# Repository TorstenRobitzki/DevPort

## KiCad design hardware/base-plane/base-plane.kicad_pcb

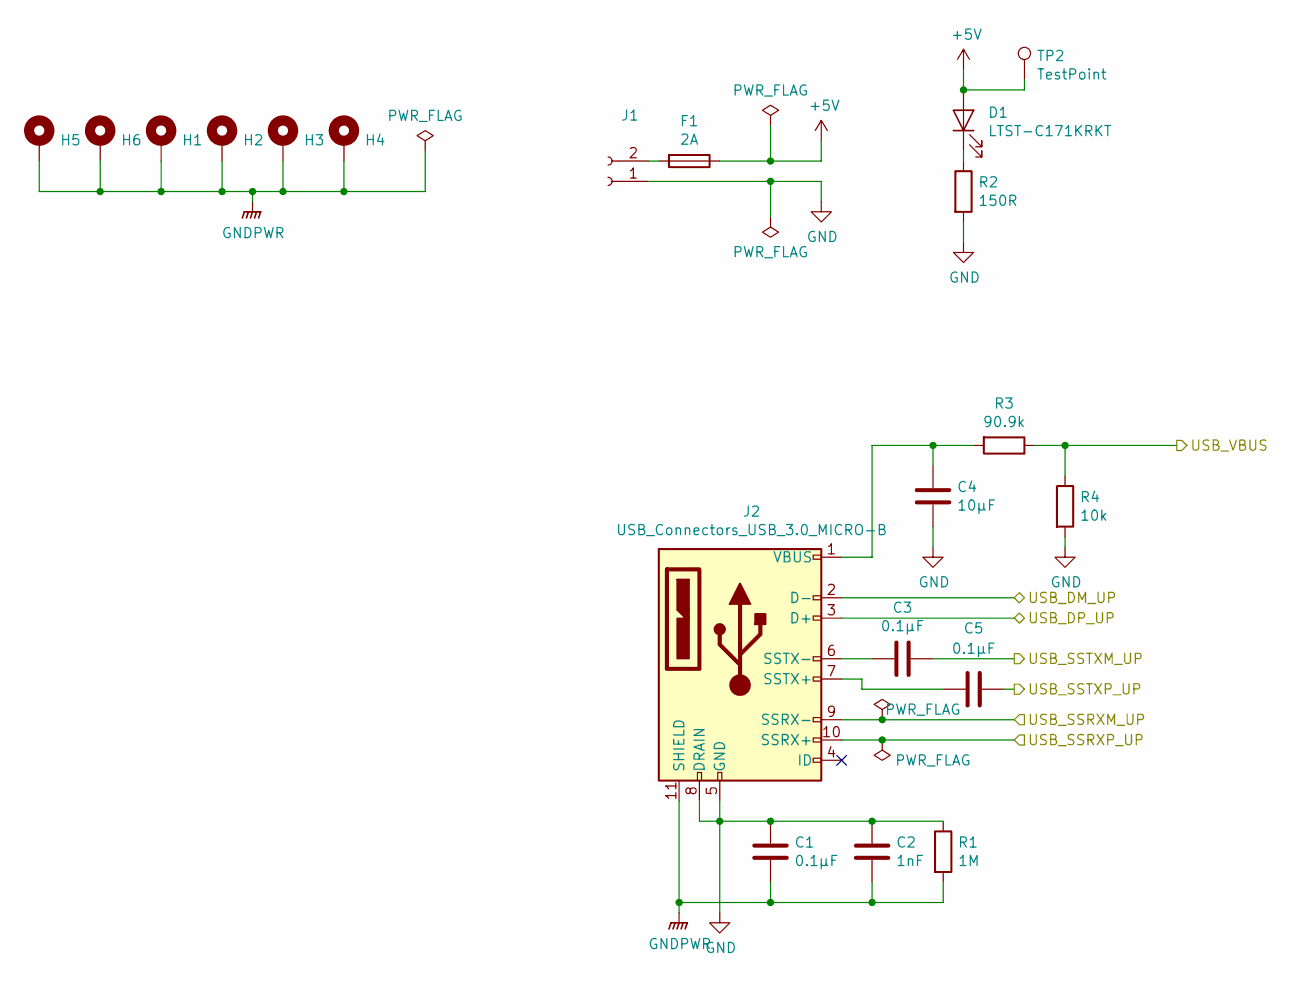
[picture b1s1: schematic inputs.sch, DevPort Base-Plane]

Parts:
C1, C3, C5: 0.1µF; C_0603_1608Metric
C2: 1nF; C_0603_1608Metric
C4: 10µF; C_0603_1608Metric
D1: LTST-C171KRKT; LED_0805_2012Metric
F1: 2A; Fuse_0603_1608Metric
H1, H2, H3, H4, H5, H6: MountingHole_Pad; MountingHole_3.2mm_M3_Pad_Via
J1: Conn_01x02_Female; Molex_Mini-Fit_Jr_5566-02A_2x01_P4.20mm_Vertical
J2: USB_Connectors_USB_3.0_MICRO-B; 692622420101
R1: 1M; R_0603_1608Metric
R2: 150R; R_0603_1608Metric
R3: 90.9k; R_0603_1608Metric
R4: 10k; R_0603_1608Metric
TP2: TestPoint; TestPoint_THTPad_1.0x1.0mm_Drill0.5mm

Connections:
+5V: D1.2 (A), F1.1, TP2.1; also elsewhere on the board
/hub/USB_DM_UP: J2.2 (D-); also elsewhere on the board
/hub/USB_DP_UP: J2.3 (D+); also elsewhere on the board
/hub/USB_SSRXM_UP: J2.9 (SSRX-); also elsewhere on the board
/hub/USB_SSRXP_UP: J2.10 (SSRX+); also elsewhere on the board
/hub/USB_SSTXM_UP: C3.1; also elsewhere on the board
/hub/USB_SSTXP_UP: C5.1; also elsewhere on the board
/hub/USB_VBUS: R3.1, R4.1; also elsewhere on the board
GND: C1.1, C2.1, C4.1, J1.1, J2.5 (GND), J2.8 (DRAIN), R1.1, R2.2, R4.2; also elsewhere on the board
GNDPWR: C1.2, C2.2, H1.1, H2.1, H3.1, H4.1, H5.1, H6.1, J2.11 (SHIELD), R1.2; also elsewhere on the board
unnamed: C3.2, J2.6 (SSTX-)
unnamed: C4.2, J2.1 (VBUS), R3.2
unnamed: C5.2, J2.7 (SSTX+)
unnamed: D1.1 (K), R2.1
unnamed: F1.2, J1.2

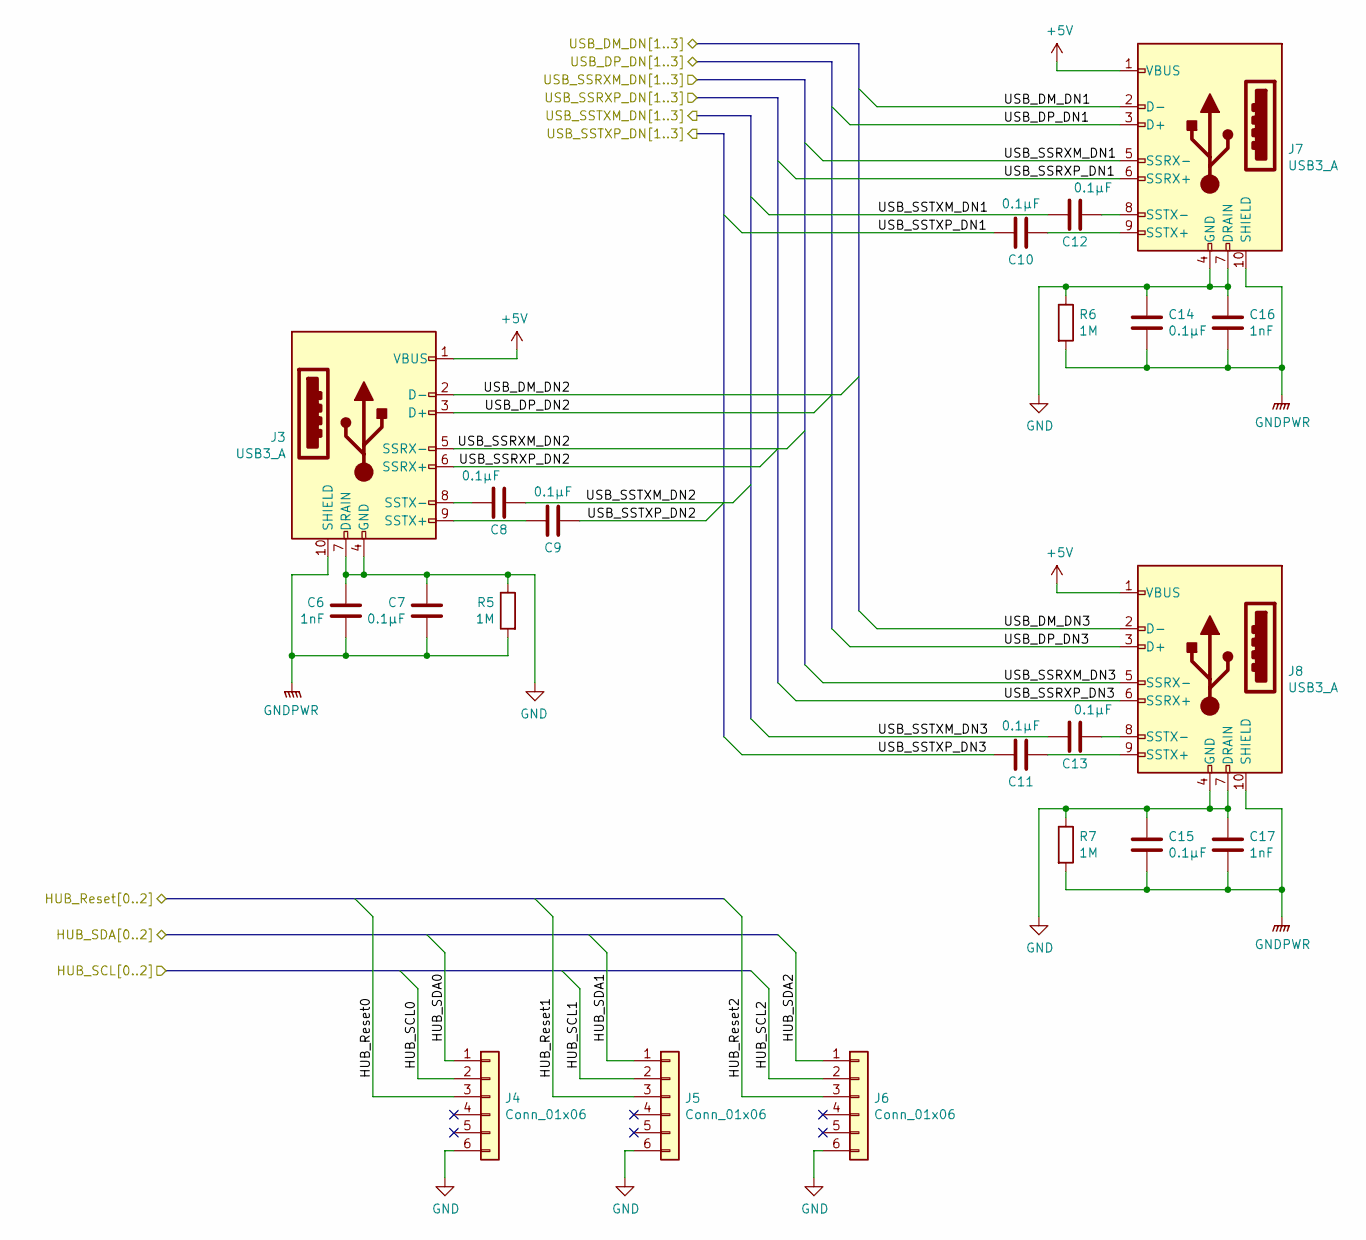
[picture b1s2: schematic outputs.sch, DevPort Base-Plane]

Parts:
C6, C16, C17: 1nF; C_0603_1608Metric
C7, C8, C9, C10, C11, C12, C13, C14, C15: 0.1µF; C_0603_1608Metric
J3, J7, J8: USB3_A; LUSB-3593-00
J4, J5, J6: Conn_01x06; PinHeader_2x03_P1.27mm_Vertical_SMD
R5, R6, R7: 1M; R_0603_1608Metric

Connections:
+5V: J3.1 (VBUS), J7.1 (VBUS), J8.1 (VBUS); also elsewhere on the board
/controller/HUB_Reset0: J4.3; also elsewhere on the board
/controller/HUB_Reset1: J5.3; also elsewhere on the board
/controller/HUB_Reset2: J6.3; also elsewhere on the board
/controller/HUB_SCL0: J4.2; also elsewhere on the board
/controller/HUB_SCL1: J5.2; also elsewhere on the board
/controller/HUB_SCL2: J6.2; also elsewhere on the board
/controller/HUB_SDA0: J4.1; also elsewhere on the board
/controller/HUB_SDA1: J5.1; also elsewhere on the board
/controller/HUB_SDA2: J6.1; also elsewhere on the board
/hub/USB_DM_DN1: J7.2 (D-); also elsewhere on the board
/hub/USB_DM_DN2: J3.2 (D-); also elsewhere on the board
/hub/USB_DM_DN3: J8.2 (D-); also elsewhere on the board
/hub/USB_DP_DN1: J7.3 (D+); also elsewhere on the board
/hub/USB_DP_DN2: J3.3 (D+); also elsewhere on the board
/hub/USB_DP_DN3: J8.3 (D+); also elsewhere on the board
/hub/USB_SSRXM_DN1: J7.5 (SSRX-); also elsewhere on the board
/hub/USB_SSRXM_DN2: J3.5 (SSRX-); also elsewhere on the board
/hub/USB_SSRXM_DN3: J8.5 (SSRX-); also elsewhere on the board
/hub/USB_SSRXP_DN1: J7.6 (SSRX+); also elsewhere on the board
/hub/USB_SSRXP_DN2: J3.6 (SSRX+); also elsewhere on the board
/hub/USB_SSRXP_DN3: J8.6 (SSRX+); also elsewhere on the board
/hub/USB_SSTXM_DN1: C12.2; also elsewhere on the board
/hub/USB_SSTXM_DN2: C8.2; also elsewhere on the board
/hub/USB_SSTXM_DN3: C13.2; also elsewhere on the board
/hub/USB_SSTXP_DN1: C10.2; also elsewhere on the board
/hub/USB_SSTXP_DN2: C9.2; also elsewhere on the board
/hub/USB_SSTXP_DN3: C11.2; also elsewhere on the board
GND: C6.1, C7.1, C14.1, C15.1, C16.1, C17.1, J3.4 (GND), J3.7 (DRAIN), J4.6, J5.6, J6.6, J7.4 (GND), J7.7 (DRAIN), J8.4 (GND), J8.7 (DRAIN), R5.1, R6.1, R7.1; also elsewhere on the board
GNDPWR: C6.2, C7.2, C14.2, C15.2, C16.2, C17.2, J3.10 (SHIELD), J7.10 (SHIELD), J8.10 (SHIELD), R5.2, R6.2, R7.2; also elsewhere on the board
unnamed: C8.1, J3.8 (SSTX-)
unnamed: C9.1, J3.9 (SSTX+)
unnamed: C10.1, J7.9 (SSTX+)
unnamed: C11.1, J8.9 (SSTX+)
unnamed: C12.1, J7.8 (SSTX-)
unnamed: C13.1, J8.8 (SSTX-)

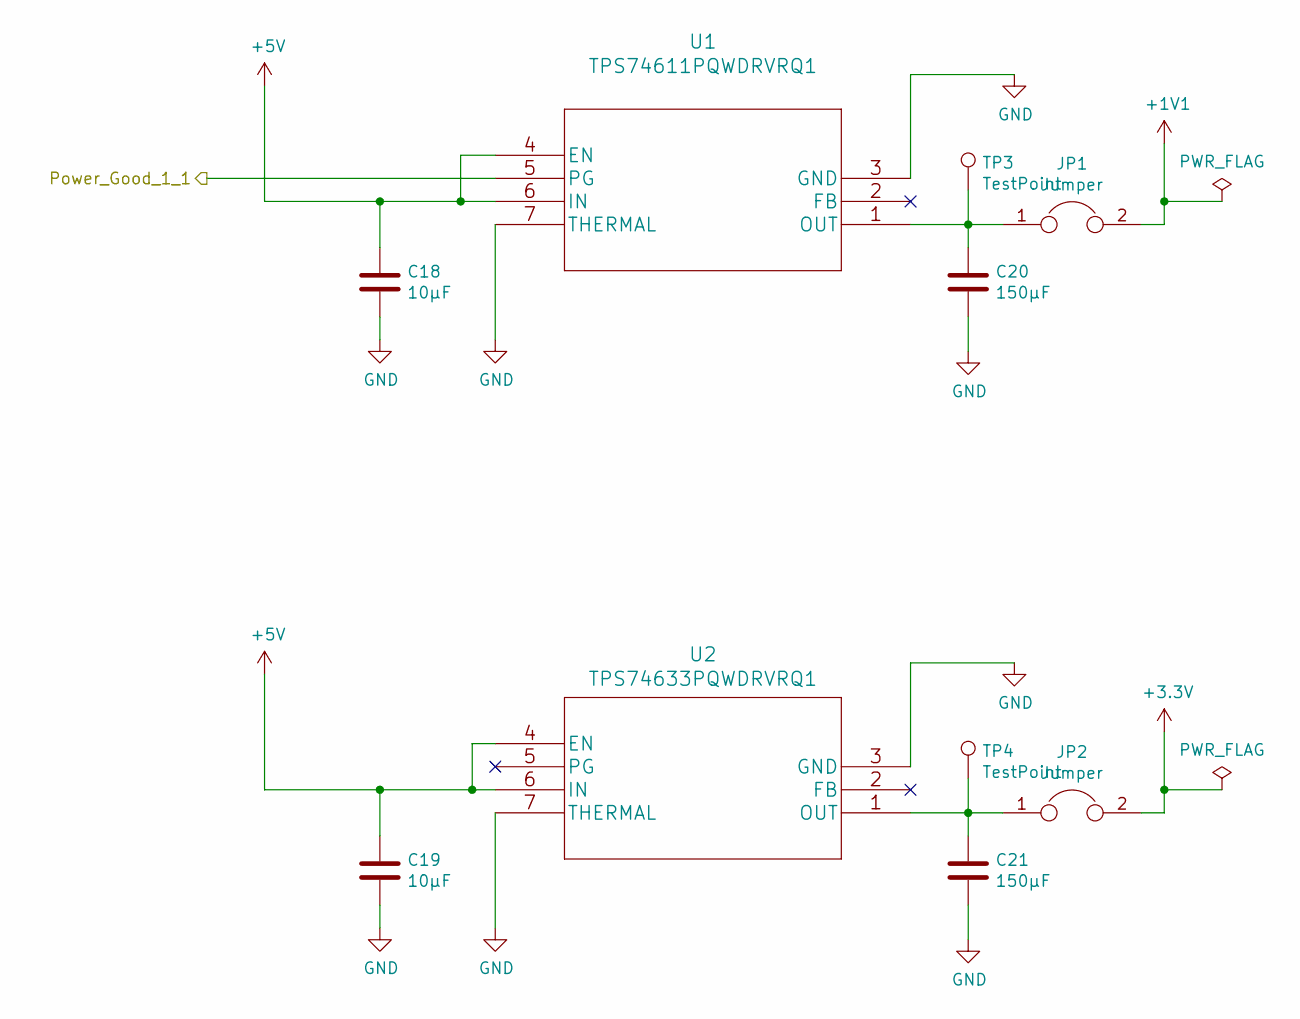
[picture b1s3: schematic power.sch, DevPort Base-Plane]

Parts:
C18, C19: 10µF; C_0603_1608Metric
C20, C21: 150µF; C_1210_3225Metric
JP1, JP2: Jumper; SolderJumper-2_P1.3mm_Bridged_RoundedPad1.0x1.5mm
TP3, TP4: TestPoint; TestPoint_THTPad_1.0x1.0mm_Drill0.5mm
U1: TPS74611PQWDRVRQ1; TPS74601PBQWDRVRQ1
U2: TPS74633PQWDRVRQ1; TPS74601PBQWDRVRQ1

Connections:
+1V1: JP1.2; also elsewhere on the board
+5V: C18.1, C19.1, U1.4 (EN), U1.6 (IN), U2.4 (EN), U2.6 (IN); also elsewhere on the board
/controller/Power_Good_1_1: U1.5 (PG); also elsewhere on the board
GND: C18.2, C19.2, C20.2, C21.2, U1.3 (GND), U1.7 (THERMAL), U2.3 (GND), U2.7 (THERMAL); also elsewhere on the board
unnamed: C20.1, JP1.1, TP3.1, U1.1 (OUT)
unnamed: C21.1, JP2.1, TP4.1, U2.1 (OUT)

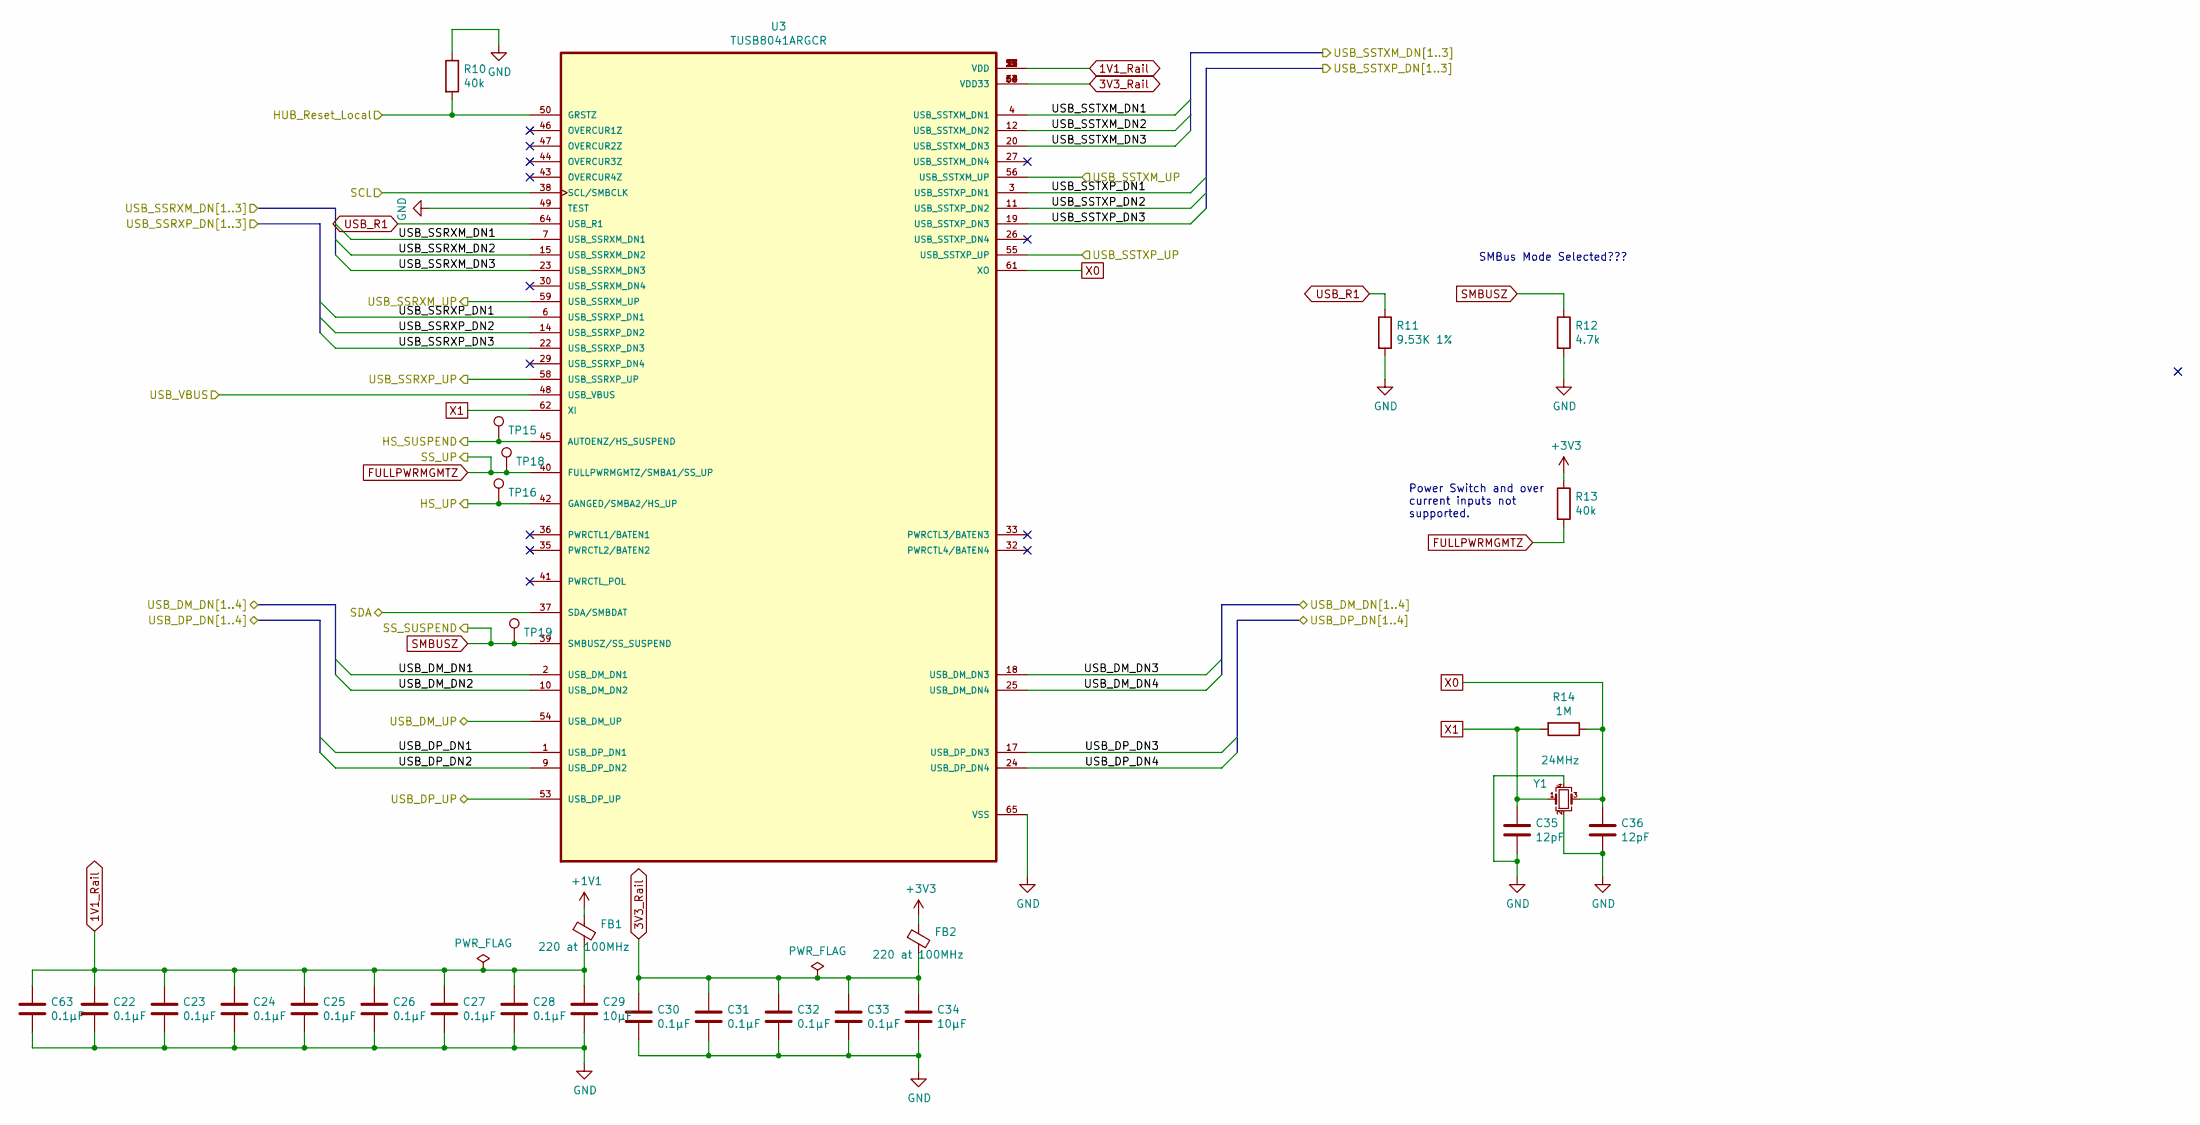
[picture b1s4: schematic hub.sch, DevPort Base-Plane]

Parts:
C22, C23, C24, C25, C26, C27, C28, C30, C31, C32, C33, C63: 0.1µF; C_0603_1608Metric
C29, C34: 10µF; C_0603_1608Metric
C35, C36: 12pF; C_0603_1608Metric
FB1, FB2: 220 at 100MHz; L_0603_1608Metric
R10, R13: 40k; R_0603_1608Metric
R11: 9.53K 1%; R_0603_1608Metric
R12: 4.7k; R_0603_1608Metric
R14: 1M; R_0603_1608Metric
TP15, TP16, TP18, TP19: TestPoint; TestPoint_THTPad_1.0x1.0mm_Drill0.5mm
U3: TUSB8041ARGCR; QFN50P900X900X100-65N
Y1: 24MHz; Crystal_SMD_3225-4Pin_3.2x2.5mm

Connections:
1V1_Rail: C22.1, C23.1, C24.1, C25.1, C26.1, C27.1, C28.1, C29.1, C63.1, FB1.2, U3.5 (VDD), U3.8 (VDD), U3.13 (VDD), U3.21 (VDD), U3.28 (VDD), U3.31 (VDD), U3.51 (VDD), U3.57 (VDD)
3V3_Rail: C30.1, C31.1, C32.1, C33.1, C34.1, FB2.2, U3.16 (VDD33), U3.34 (VDD33), U3.52 (VDD33), U3.63 (VDD33)
+1V1: FB1.1; also elsewhere on the board
/hub/USB_DM_DN1: U3.2 (USB_DM_DN1); also elsewhere on the board
/hub/USB_DM_DN2: U3.10 (USB_DM_DN2); also elsewhere on the board
/hub/USB_DM_DN3: U3.18 (USB_DM_DN3); also elsewhere on the board
/hub/USB_DM_UP: U3.54 (USB_DM_UP); also elsewhere on the board
/hub/USB_DP_DN1: U3.1 (USB_DP_DN1); also elsewhere on the board
/hub/USB_DP_DN2: U3.9 (USB_DP_DN2); also elsewhere on the board
/hub/USB_DP_DN3: U3.17 (USB_DP_DN3); also elsewhere on the board
/hub/USB_DP_UP: U3.53 (USB_DP_UP); also elsewhere on the board
/hub/USB_SSRXM_DN1: U3.7 (USB_SSRXM_DN1); also elsewhere on the board
/hub/USB_SSRXM_DN2: U3.15 (USB_SSRXM_DN2); also elsewhere on the board
/hub/USB_SSRXM_DN3: U3.23 (USB_SSRXM_DN3); also elsewhere on the board
/hub/USB_SSRXM_UP: U3.59 (USB_SSRXM_UP); also elsewhere on the board
/hub/USB_SSRXP_DN1: U3.6 (USB_SSRXP_DN1); also elsewhere on the board
/hub/USB_SSRXP_DN2: U3.14 (USB_SSRXP_DN2); also elsewhere on the board
/hub/USB_SSRXP_DN3: U3.22 (USB_SSRXP_DN3); also elsewhere on the board
/hub/USB_SSRXP_UP: U3.58 (USB_SSRXP_UP); also elsewhere on the board
/hub/USB_SSTXM_DN1: U3.4 (USB_SSTXM_DN1); also elsewhere on the board
/hub/USB_SSTXM_DN2: U3.12 (USB_SSTXM_DN2); also elsewhere on the board
/hub/USB_SSTXM_DN3: U3.20 (USB_SSTXM_DN3); also elsewhere on the board
/hub/USB_SSTXM_UP: U3.56 (USB_SSTXM_UP); also elsewhere on the board
/hub/USB_SSTXP_DN1: U3.3 (USB_SSTXP_DN1); also elsewhere on the board
/hub/USB_SSTXP_DN2: U3.11 (USB_SSTXP_DN2); also elsewhere on the board
/hub/USB_SSTXP_DN3: U3.19 (USB_SSTXP_DN3); also elsewhere on the board
/hub/USB_SSTXP_UP: U3.55 (USB_SSTXP_UP); also elsewhere on the board
FULLPWRMGMTZ: R13.2, TP18.1, U3.40 (FULLPWRMGMTZ/SMBA1/SS_UP); also elsewhere on the board
GND: C22.2, C23.2, C24.2, C25.2, C26.2, C27.2, C28.2, C29.2, C30.2, C31.2, C32.2, C33.2, C34.2, C35.2, C36.2, C63.2, R10.1, R11.2, R12.2, U3.49 (TEST), U3.65 (VSS), Y1.2, Y1.4; also elsewhere on the board
HS_SUSPEND: TP15.1, U3.45 (AUTOENZ/HS_SUSPEND); also elsewhere on the board
HS_UP: TP16.1, U3.42 (GANGED/SMBA2/HS_UP); also elsewhere on the board
HUB_Reset_Local: R10.2, U3.50 (GRSTZ); also elsewhere on the board
unnamed 105: U3.48 (USB_VBUS); also elsewhere on the board
SCL: U3.38 (SCL/SMBCLK); also elsewhere on the board
SDA: U3.37 (SDA/SMBDAT); also elsewhere on the board
SMBUSZ: R12.1, TP19.1, U3.39 (SMBUSZ/SS_SUSPEND); also elsewhere on the board
USB_DM_DN4: U3.25 (USB_DM_DN4); also elsewhere on the board
USB_DP_DN4: U3.24 (USB_DP_DN4); also elsewhere on the board
USB_R1: R11.1, U3.64 (USB_R1)
X0: C36.1, R14.1, U3.61 (XO), Y1.3
X1: C35.1, R14.2, U3.62 (XI), Y1.1

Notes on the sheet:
SMBus Mode Selected???
Power Switch and over current inputs not supported.

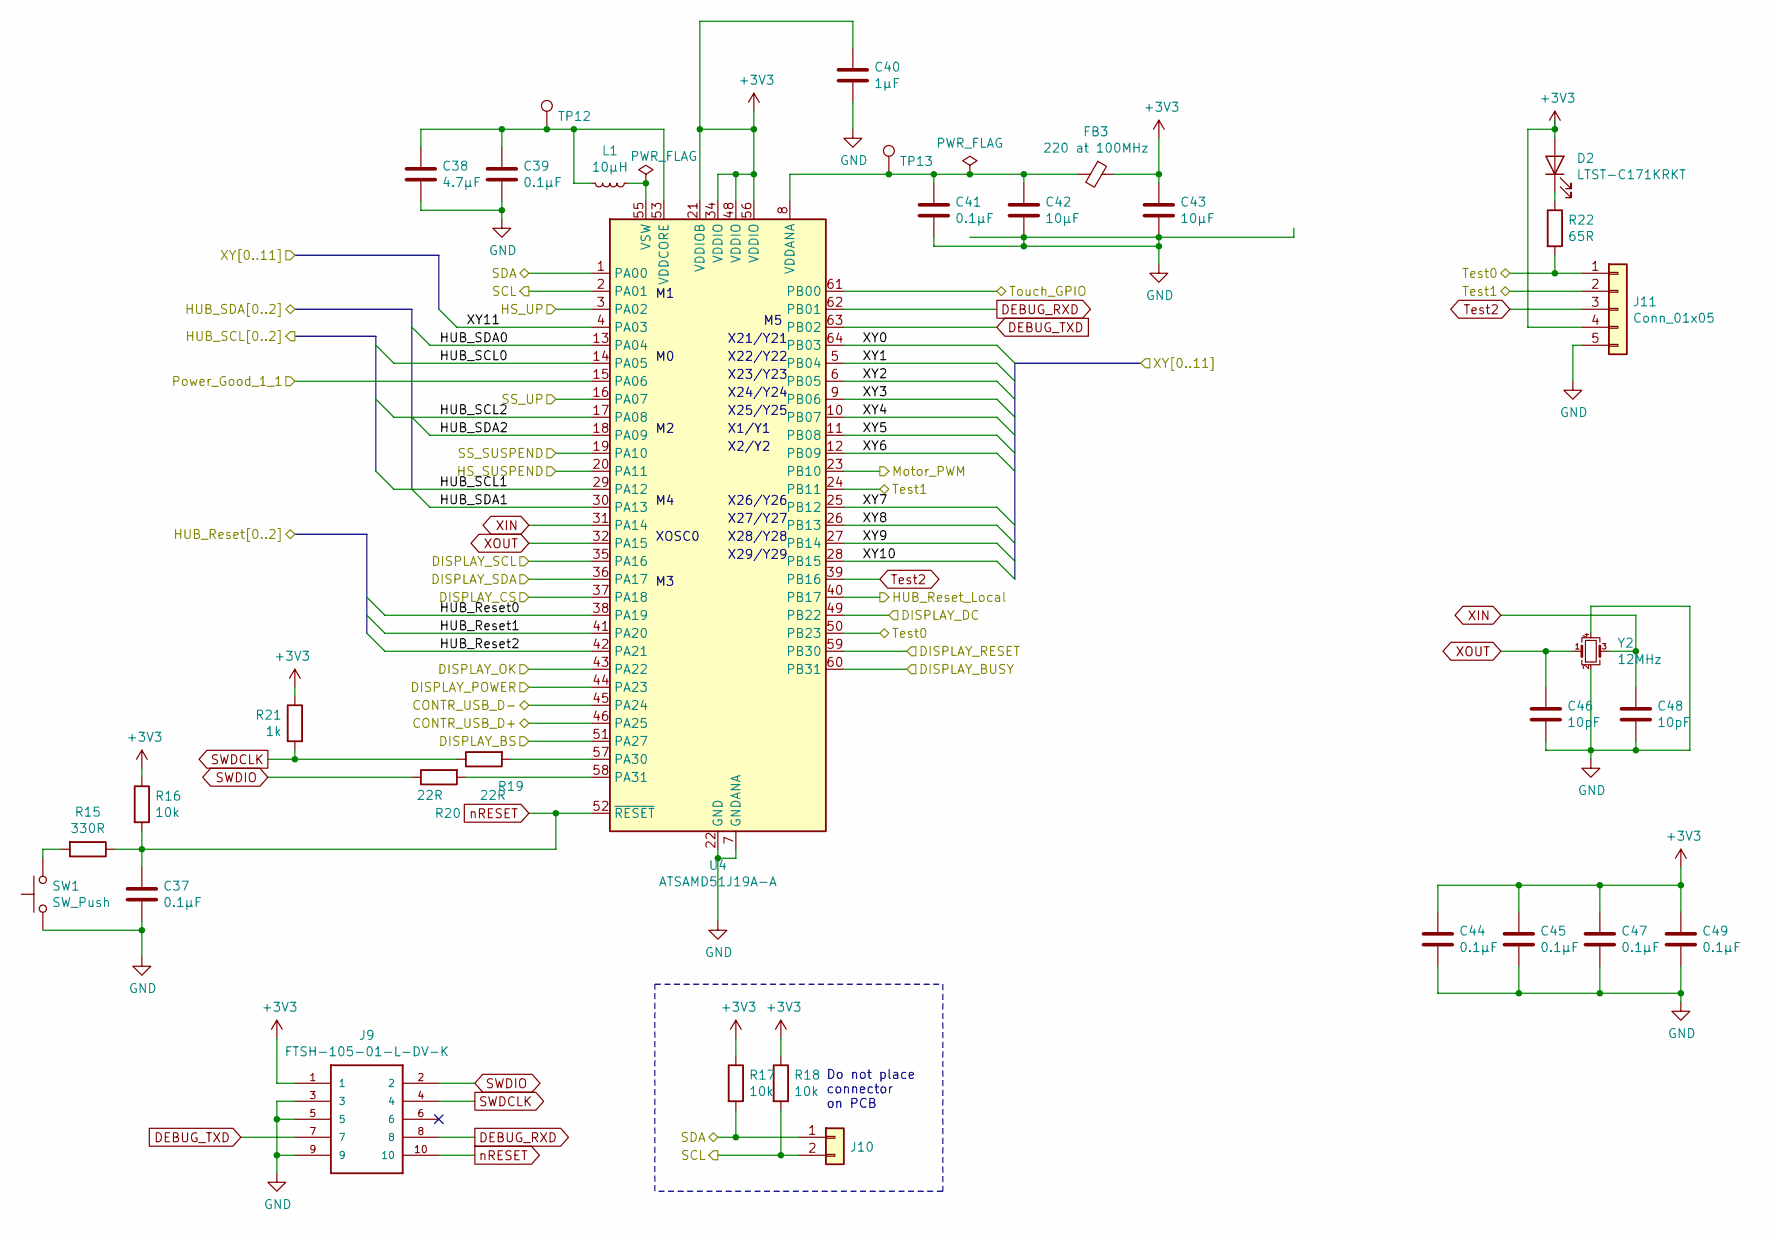
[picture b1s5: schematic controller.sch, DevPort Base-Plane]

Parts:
C37, C39, C41, C44, C45, C47, C49: 0.1µF; C_0603_1608Metric
C38: 4.7µF; C_0603_1608Metric
C40: 1µF; C_0603_1608Metric
C42, C43: 10µF; C_0603_1608Metric
C46, C48: 10pF; C_0603_1608Metric
D2: LTST-C171KRKT; LED_0805_2012Metric
FB3: 220 at 100MHz; L_0603_1608Metric
J9: FTSH-105-01-L-DV-K; SAMTEC_FTSH-105-XX-X-DV
J10: Conn_01x02; PinHeader_1x02_P2.54mm_Vertical
J11: Conn_01x05; PinHeader_1x05_P2.54mm_Vertical
L1: 10µH; IND_LQH32PZ100MNCL
R15: 330R; R_0603_1608Metric
R16, R17, R18: 10k; R_0603_1608Metric
R19, R20: 22R; R_0603_1608Metric
R21: 1k; R_0603_1608Metric
R22: 65R; R_0603_1608Metric
SW1: SW_Push; Panasonic_EVQPUJ_EVQPUA
TP12, TP13: TestPoint; TestPoint_THTPad_1.0x1.0mm_Drill0.5mm
U4: ATSAMD51J19A-A; TQFP-64_10x10mm_P0.5mm
Y2: 12MHz; Crystal_SMD_2520-4Pin_2.5x2.0mm

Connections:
/controller/DISPLAY_BS: U4.51 (PA27); also elsewhere on the board
/controller/DISPLAY_CS: U4.37 (PA18); also elsewhere on the board
/controller/DISPLAY_DC: U4.49 (PB22); also elsewhere on the board
/controller/DISPLAY_OK: U4.43 (PA22); also elsewhere on the board
/controller/DISPLAY_POWER: U4.44 (PA23); also elsewhere on the board
/controller/DISPLAY_SCL: U4.35 (PA16); also elsewhere on the board
/controller/DISPLAY_SDA: U4.36 (PA17); also elsewhere on the board
/controller/HUB_Reset0: U4.38 (PA19); also elsewhere on the board
/controller/HUB_Reset1: U4.41 (PA20); also elsewhere on the board
/controller/HUB_Reset2: U4.42 (PA21); also elsewhere on the board
/controller/HUB_SCL0: U4.14 (PA05); also elsewhere on the board
/controller/HUB_SCL1: U4.29 (PA12); also elsewhere on the board
/controller/HUB_SCL2: U4.17 (PA08); also elsewhere on the board
/controller/HUB_SDA0: U4.13 (PA04); also elsewhere on the board
/controller/HUB_SDA1: U4.30 (PA13); also elsewhere on the board
/controller/HUB_SDA2: U4.18 (PA09); also elsewhere on the board
/controller/Motor_PWM: U4.23 (PB10); also elsewhere on the board
/controller/Power_Good_1_1: U4.15 (PA06); also elsewhere on the board
/controller/Test0: J11.1, R22.2, U4.50 (PB23); also elsewhere on the board
/controller/Test1: J11.2, U4.24 (PB11)
/controller/Touch_GPIO: U4.61 (PB00); also elsewhere on the board
/controller/XY0: U4.64 (PB03); also elsewhere on the board
/controller/XY1: U4.5 (PB04); also elsewhere on the board
/controller/XY2: U4.6 (PB05); also elsewhere on the board
/controller/XY3: U4.9 (PB06); also elsewhere on the board
/controller/XY4: U4.10 (PB07); also elsewhere on the board
/controller/XY5: U4.11 (PB08); also elsewhere on the board
/controller/XY6: U4.12 (PB09); also elsewhere on the board
/controller/XY7: U4.25 (PB12); also elsewhere on the board
/controller/XY8: U4.26 (PB13); also elsewhere on the board
/controller/XY9: U4.27 (PB14); also elsewhere on the board
/controller/XY10: U4.28 (PB15); also elsewhere on the board
/controller/XY11: U4.4 (PA03); also elsewhere on the board
DEBUG_RXD: J9.8, U4.62 (PB01)
DEBUG_TXD: J9.7, U4.63 (PB02)
FULLPWRMGMTZ: U4.16 (PA07); also elsewhere on the board
GND: C37.2, C38.2, C39.2, C40.2, C41.2, C42.2, C43.2, C44.2, C45.2, C46.2, C47.2, C48.2, C49.2, J9.3, J9.5, J9.9, J11.5, SW1.1, U4.7 (GNDANA), U4.22 (GND), U4.33 (GND), U4.47 (GND), U4.54 (GND), Y2.2, Y2.4; also elsewhere on the board
HS_SUSPEND: U4.20 (PA11); also elsewhere on the board
HS_UP: U4.3 (PA02); also elsewhere on the board
HUB_Reset_Local: U4.40 (PB17); also elsewhere on the board
unnamed: C38.1, C39.1, L1.2, TP12.1, U4.53 (VDDCORE)
unnamed: C41.1, C42.1, FB3.2, TP13.1, U4.8 (VDDANA)
unnamed: D2.1 (K), R22.1
unnamed: L1.1, U4.55 (VSW)
unnamed: R15.2, SW1.2
SCL: J10.2, R18.2, U4.2 (PA01); also elsewhere on the board
SDA: J10.1, R17.2, U4.1 (PA00); also elsewhere on the board
SMBUSZ: U4.19 (PA10); also elsewhere on the board
SWDCLK: J9.4, R19.1, R21.2
SWDIO: J9.2, R20.1
Test2: J11.3, U4.39 (PB16)
USB_DM_DN4: U4.45 (PA24); also elsewhere on the board
USB_DP_DN4: U4.46 (PA25); also elsewhere on the board
XIN: C48.1, U4.31 (PA14), Y2.3
XOUT: C46.1, U4.32 (PA15), Y2.1
nRESET: C37.1, J9.10, R15.1, R16.2, U4.52 (~RESET)

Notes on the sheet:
XOSC0
X25/Y25
X1/Y1
X2/Y2
X26/Y26
X27/Y27
X28/Y28
X29/Y29
Do not place connector on PCB
X24/Y24
X23/Y23
X22/Y22
X21/Y21

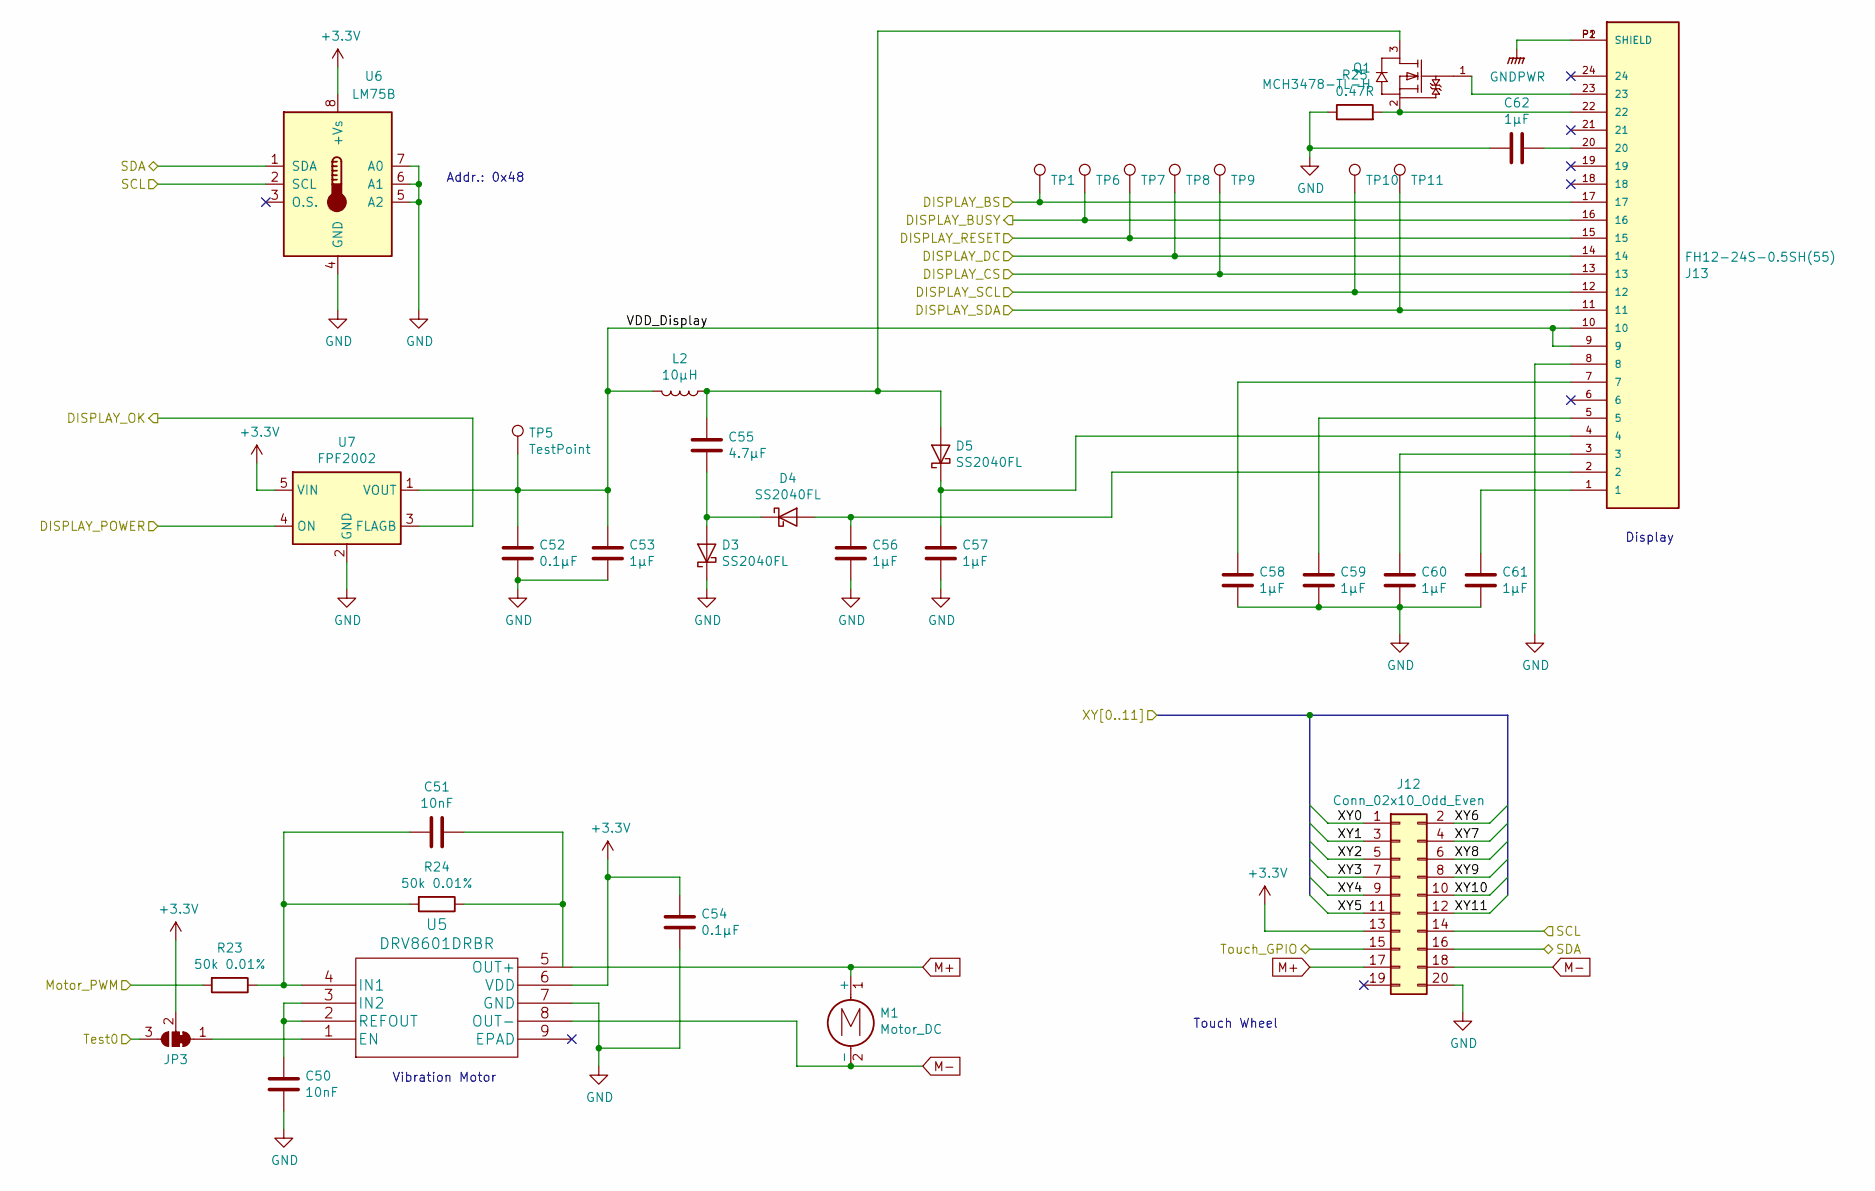
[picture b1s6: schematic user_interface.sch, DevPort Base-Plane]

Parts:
C50, C51: 10nF; C_0603_1608Metric
C52, C54: 0.1µF; C_0603_1608Metric
C53, C56, C57, C58, C59, C60, C61, C62: 1µF; C_0603_1608Metric
C55: 4.7µF; C_0603_1608Metric
D3, D4, D5: SS2040FL; D_SOD-123F
J12: Conn_02x10_Odd_Even; Molex_SlimStack_55560-0201_2x10_P0.50mm_Vertical
J13: FH12-24S-0.5SH(55); HRS_FH12-24S-0.5SH(55)
JP3: SolderJumper_3_Bridged12; SolderJumper-3_P1.3mm_Bridged12_RoundedPad1.0x1.5mm
L2: 10µH; IND_LQH32PZ100MNCL
M1: Motor_DC; PinHeader_1x02_P2.54mm_Vertical
Q1: MCH3478-TL-H; On_Semiconductor-MCH3478-TL-H-Manufacturer_Recommended
R23, R24: 50k 0.01%; R_0603_1608Metric
R25: 0.47R; R_0603_1608Metric
TP1, TP5, TP6, TP7, TP8, TP9, TP10, TP11: TestPoint; TestPoint_THTPad_1.0x1.0mm_Drill0.5mm
U5: DRV8601DRBR
U6: LM75B; TSSOP-8_3x3mm_P0.65mm
U7: FPF2002; SOT-353_SC-70-5

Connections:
/controller/DISPLAY_BS: J13.17, TP1.1; also elsewhere on the board
/controller/DISPLAY_CS: J13.13, TP9.1; also elsewhere on the board
/controller/DISPLAY_DC: J13.14, TP8.1; also elsewhere on the board
/controller/DISPLAY_OK: U7.3 (FLAGB); also elsewhere on the board
/controller/DISPLAY_POWER: U7.4 (ON); also elsewhere on the board
/controller/DISPLAY_SCL: J13.12, TP10.1; also elsewhere on the board
/controller/DISPLAY_SDA: J13.11, TP11.1; also elsewhere on the board
/controller/Motor_PWM: R23.2; also elsewhere on the board
/controller/Test0: JP3.3 (B); also elsewhere on the board
/controller/Touch_GPIO: J12.15; also elsewhere on the board
/controller/XY0: J12.1; also elsewhere on the board
/controller/XY1: J12.3; also elsewhere on the board
/controller/XY2: J12.5; also elsewhere on the board
/controller/XY3: J12.7; also elsewhere on the board
/controller/XY4: J12.9; also elsewhere on the board
/controller/XY5: J12.11; also elsewhere on the board
/controller/XY6: J12.2; also elsewhere on the board
/controller/XY7: J12.4; also elsewhere on the board
/controller/XY8: J12.6; also elsewhere on the board
/controller/XY9: J12.8; also elsewhere on the board
/controller/XY10: J12.10; also elsewhere on the board
/controller/XY11: J12.12; also elsewhere on the board
/user_interface/VDD_Display: C52.1, C53.1, J13.9, J13.10, L2.2, TP5.1, U7.1 (VOUT)
GND: C50.2, C52.2, C53.2, C54.2, C56.2, C57.2, C58.1, C59.1, C60.2, C61.2, C62.2, D3.1 (K), J12.20, J13.8, R25.1, U5.7 (GND), U6.4 (GND), U6.5 (A2), U6.6 (A1), U6.7 (A0), U7.2 (GND); also elsewhere on the board
GNDPWR: J13.P1 (SHIELD), J13.P2 (SHIELD); also elsewhere on the board
M+: J12.17, M1.1 (+), U5.5 (OUT+)
M-: J12.18, M1.2 (-), U5.8 (OUT-)
unnamed: C50.1, U5.2 (REFOUT), U5.3 (IN2)
unnamed: C51.1, R24.1
unnamed: C51.2, R23.1, R24.2, U5.4 (IN1)
unnamed: C55.1, D5.2 (A), L2.1, Q1.3 (D)
unnamed: C55.2, D3.2 (A), D4.1 (K)
unnamed: C56.1, D4.2 (A), J13.2
unnamed: C57.1, D5.1 (K), J13.4
unnamed: C58.2, J13.7
unnamed: C59.2, J13.5
unnamed: C60.1, J13.3
unnamed: C61.1, J13.1
unnamed: C62.1, J13.20
unnamed: J13.22, Q1.2 (S), R25.2
unnamed: J13.23, Q1.1 (G)
unnamed: JP3.1 (A), U5.1 (EN)
SCL: J12.14, U6.2 (SCL); also elsewhere on the board
SDA: J12.16, U6.1 (SDA); also elsewhere on the board

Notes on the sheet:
Display
Touch Wheel
Addr.: 0x48
Vibration Motor

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
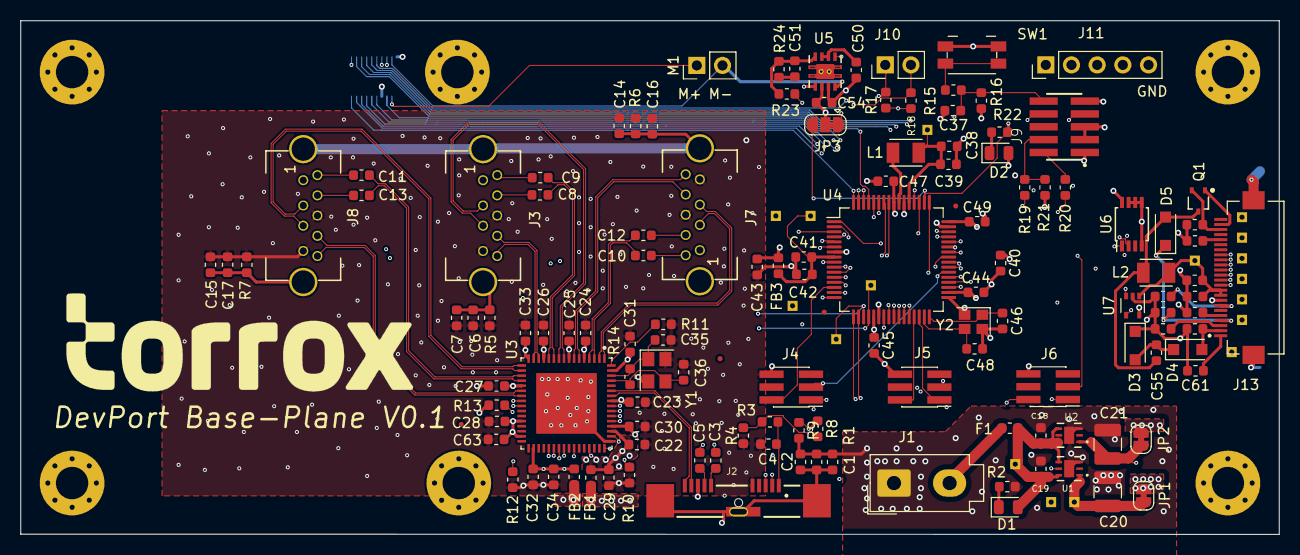
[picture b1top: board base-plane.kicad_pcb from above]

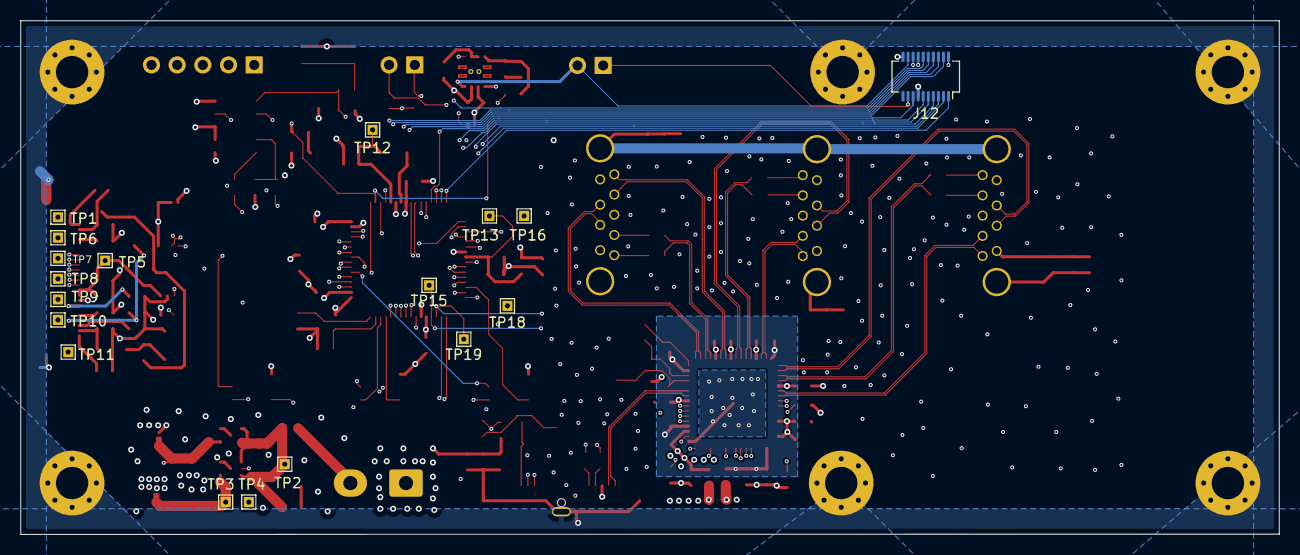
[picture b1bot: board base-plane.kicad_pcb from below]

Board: 6 copper layers, 124.5 x 50.8 mm, 150 parts (18 on the bottom side), 126 nets.

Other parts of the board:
R8: 90.9k 1%; R_0603_1608Metric
R9: 10k 1%; R_0603_1608Metric

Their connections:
/hub/USB_VBUS: R8.2; also elsewhere on the board
GND: R9.2; also elsewhere on the board
unnamed 105: R8.1, R9.1; also elsewhere on the board

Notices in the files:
parts and their libraries:
Copyright 2016 Accelerated Designs. All rights reserved.
